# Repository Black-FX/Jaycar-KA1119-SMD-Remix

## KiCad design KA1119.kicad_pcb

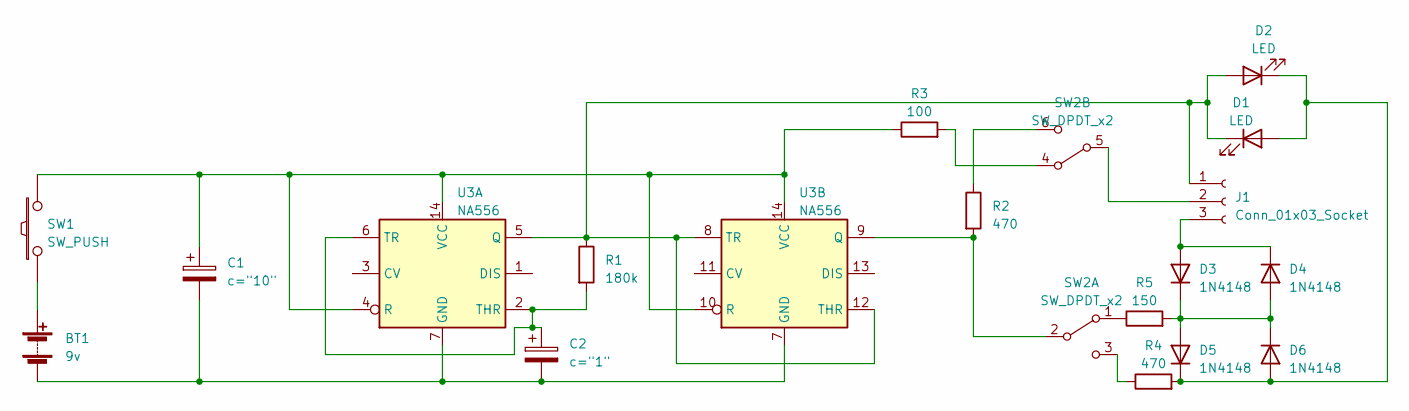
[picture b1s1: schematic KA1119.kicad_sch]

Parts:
BT1: 9v; PinHeader_1x02_P1.27mm_Vertical; Mouser Part 60563-01 HM-9VB
C1: c="10"; CP_Radial_D4.0mm_P1.50mm
C2: c="1"; CP_Radial_D4.0mm_P1.50mm
D1, D2: LED; LED_0603_1608Metric_Pad1.05x0.95mm_HandSolder
D3, D4, D5, D6: 1N4148; D_SOD-323_HandSoldering; Mouser Part 1N4148WS-7-F
J1: Conn_01x03_Socket; PinSocket_1x03_P1.27mm_Vertical
R1: 180k; R_0603_1608Metric_Pad0.98x0.95mm_HandSolder
R2, R4: 470; R_0603_1608Metric_Pad0.98x0.95mm_HandSolder
R3: 100; R_0603_1608Metric_Pad0.98x0.95mm_HandSolder
R5: 150; R_0603_1608Metric_Pad0.98x0.95mm_HandSolder
SW1: SW_PUSH; SW_PUSH_6mm
SW2: SW_DPDT_x2; SW_DPDT_CK_JS202011JCQN
U3: NA556; SOIC-14_3.9x8.7mm_P1.27mm

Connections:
unnamed 0: BT1.1 (+), SW1.1; also elsewhere on the board
unnamed 1: BT1.2 (-), C1.2, C2.2, U3.7 (GND); also elsewhere on the board
unnamed: D1.2 (A), D2.1 (K), D5.1 (K), D6.2 (A), R4.2
unnamed: D1.1 (K), D2.2 (A), J1.1, R1.1, U3.5 (Q), U3.8 (TR), U3.12 (THR)
unnamed: D3.2 (A), D4.1 (K), J1.3
unnamed: D3.1 (K), D4.2 (A), D5.2 (A), D6.1 (K), R5.2
unnamed: J1.2, SW2.5 (B)
unnamed: R5.1, SW2.1 (A)
unnamed: R2.2, SW2.2 (B), U3.9 (Q)
unnamed: R4.1, SW2.3 (C)
unnamed: R3.2, SW2.4 (A)
unnamed: R2.1, SW2.6 (C)
unnamed: C1.1, R3.1, SW1.2, U3.4 (R), U3.10 (R), U3.14 (VCC)
unnamed: C2.1, R1.2, U3.2 (THR), U3.6 (TR)

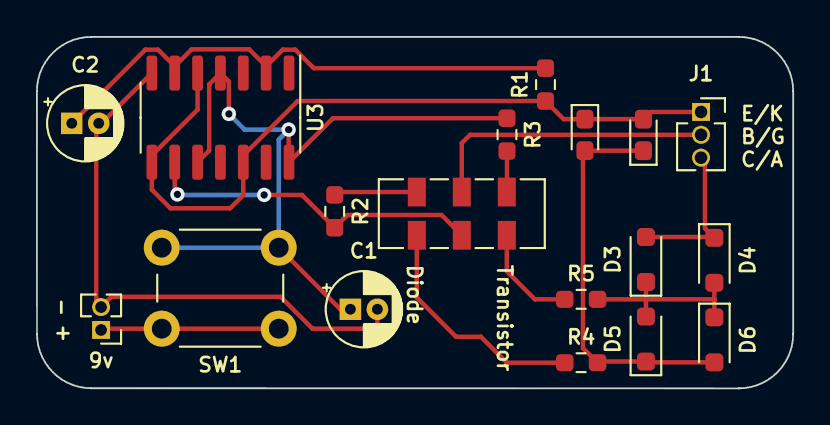
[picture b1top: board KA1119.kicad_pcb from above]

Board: 2 copper layers, 42.0 x 19.5 mm, 18 parts (0 on the bottom side), 14 nets.

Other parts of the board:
9v: 9v; PinHeader_1x02_P1.27mm_Vertical

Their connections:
unnamed 0: 9v.1 (+); also elsewhere on the board
unnamed 1: 9v.2 (-); also elsewhere on the board
